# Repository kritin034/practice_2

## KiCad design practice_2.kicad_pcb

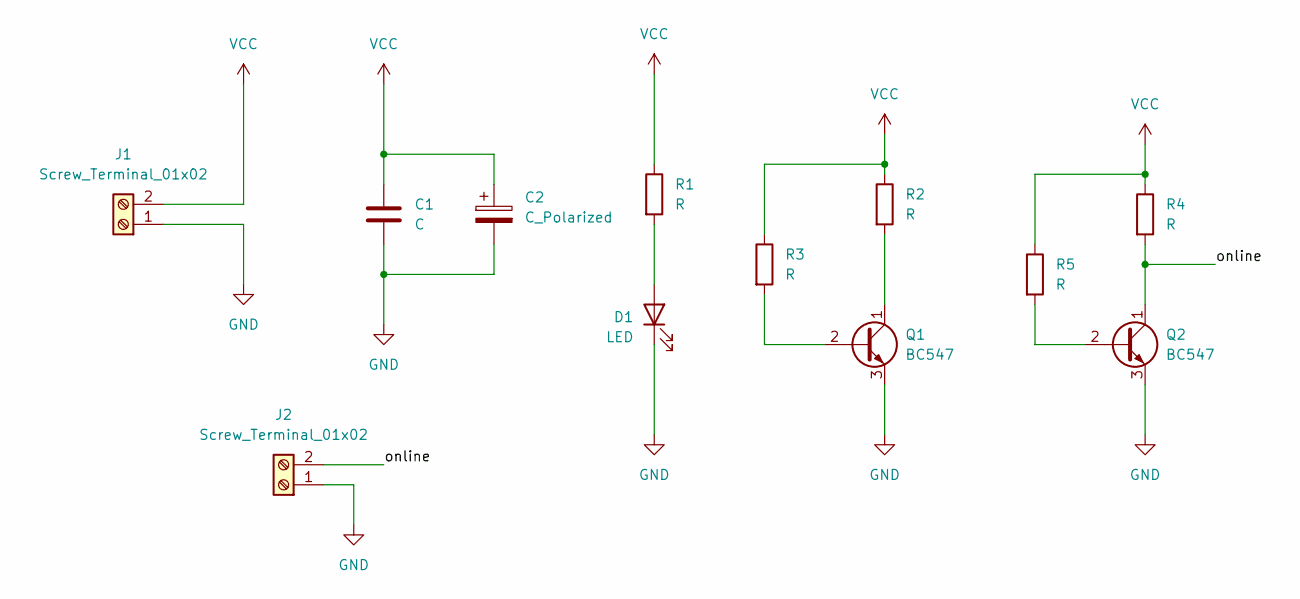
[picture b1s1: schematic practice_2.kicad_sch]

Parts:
C1: C; C_Disc_D5.0mm_W2.5mm_P5.00mm
C2: C_Polarized; CP_Radial_D12.5mm_P5.00mm
D1: LED; LED_D3.0mm
J1: Screw_Terminal_01x02; TerminalBlock_MaiXu_MX126-5.0-02P_1x02_P5.00mm
J2: Screw_Terminal_01x02
Q1, Q2: BC547; TO-92_Inline
R1, R2, R3, R4, R5: R; R_0508_1220Metric_Pad1.12x2.15mm_HandSolder

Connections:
/online: J2.2, Q2.1 (C), R4.2
GND: C1.2, C2.2, D1.1 (K), J1.1, J2.1, Q1.3 (E), Q2.3 (E); also elsewhere on the board
unnamed: D1.2 (A), R1.2
unnamed: Q1.2 (B), R3.2
unnamed: Q1.1 (C), R2.2
unnamed: Q2.2 (B), R5.2
VCC: C1.1, C2.1, J1.2, R1.1, R2.1, R3.1, R4.1, R5.1; also elsewhere on the board

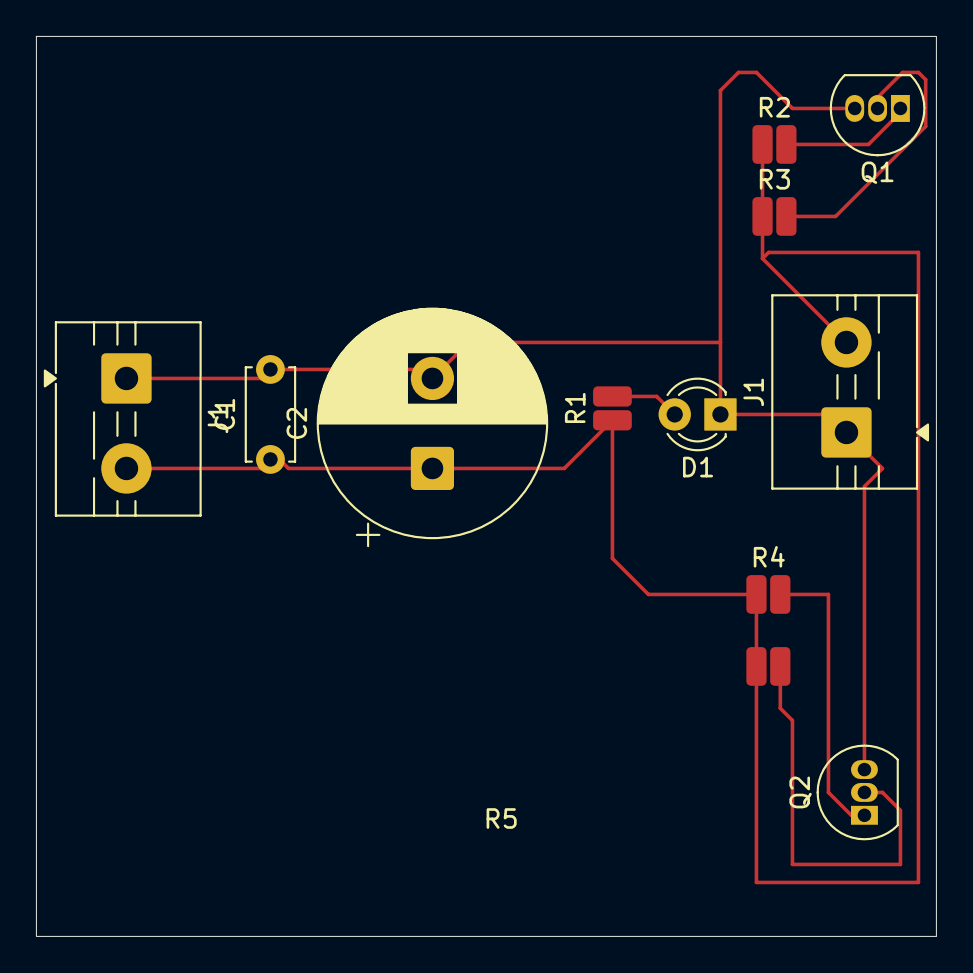
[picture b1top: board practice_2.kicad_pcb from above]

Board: 2 copper layers, 50.0 x 50.0 mm, 12 parts (0 on the bottom side), 7 nets.

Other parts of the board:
J1#2: Screw_Terminal_01x02; TerminalBlock_MaiXu_MX126-5.0-02P_1x02_P5.00mm

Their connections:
GND: J1#2.1; also elsewhere on the board
VCC: J1#2.2; also elsewhere on the board
